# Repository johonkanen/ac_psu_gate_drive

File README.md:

# ac_psu_gate_drive

KiCad 10.0.7 conversion of the Proteus half-bridge gate-driver board
`gate_drive_power_asym_fb_v3_ee10` (2 × Si8271 isolated gate drivers, IXDD609 driving a hand-wound
toroid that supplies the two floating +/− gate rails; 22.4 × 34.9 mm, 2 layers). The board plugs face
to face into the ac_psu baseboard's J1–J4/J6/J8 (`~/dev/ac_psu_kicad`).

- `kicad/gate_drive.kicad_pro` – schematic (2 sheets, generated by `tools/sheets/sheetNN.py`) and PCB
  (`tools/make_pcb.sh`, rebuilt from the Proteus gerbers).
- `fab/` – JLCPCB BOM / CPL / gerbers and the hand-fit list (`fab/README.md`).
- `tools/check_all.sh` – every check (IPC netlist, ERC, footprints, board, DRC, IPC-356 diff,
  gerber round trip); must end with `ALL CHECKS PASSED`.
- `dcm/` – the DCM variant `gate_drive_power_dcm_fb_v3_ee10` (Q1 MMBT3904 primary switch instead of
  DRV3), converted the same way as a self-contained subproject; see `dcm/README.md`.
- `PLAN.md`, `STATUS.md`, `next_prompt.md` – plan, state and findings, next session prompt.

Tools: the proteus2kicad submodule `tools/p2k` (`git submodule update --init`); KiCad AppImage
`~/kicad/kicad-10.0.7-x86_64.AppImage` (never run it with `--version`).

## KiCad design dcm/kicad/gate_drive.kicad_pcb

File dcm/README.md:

# dcm – DCM variant of the gate-driver board

KiCad 10.0.7 conversion of the Proteus board `gate_drive_power_dcm_fb_v3_ee10` (2021-03-22). It is
the asym board of the repository root with the toroid primary driver replaced: instead of the
IXDD609 (DRV3) driving the primary through C12, a single NPN Q1 (MMBT3904) switches the primary
from 15V (J1 = 15V, J2 = collector), with the leakage/flyback energy clamped by R7 – D9 into
C9 ‖ R14 back to 15V. Same outline (22.4 × 34.9 mm), same J9 pinout, same gate drivers and rectifiers.

Converted 2026-11-03 (user: "convert the dcm version too"), same method and tools as the root board
(proteus2kicad playbook phases 0–4, submodule `../tools/p2k` through the symlink `tools/p2k`).
This folder is self-contained: its own `p2k_config.py`, so every tool run inside `dcm/` works on
this board. `tools/check_all.sh` must end with `ALL CHECKS PASSED`.

## Sources (`source/`)

`/mnt/c/Users/jaarh/Sync/proteus_projektit/Projects/gate_drive_power_asym_fb/V3_ee10/dcm/`: the
`.pdsprj` (Proteus 8.12 SP0) and the CADCAM zip (unpacked to `source/cadcam/`; identical copies in
`Sync_backup` and `D:\Sync_vamuuskopio`). **No PDF print exists** for this project.

IPC-D-356A: 135 records, 26 nets, 43 parts, 16 vias 0.381/0.254, no N/C, no holes.
Against the asym board: removed DRV3, C7 (4.7u 1206), C12 (100n); added Q1 MMBT3904, R7 10k,
R13 2.2k, R14 10k, C9 100n, D9 ZLLS400TA (values from ROOT.DSN); R11 is now the base resistor
(was the PWM_TRANS pull-down; R13 is that now). C8, R9, R11 and D6 moved; the copper around the primary switch and 5 vias differ.

## How it differs from the root conversion

- **Pages without a PDF:** `tools/make_part_map.py` puts the parts of the asym PDF page 1 on sheet 1
  (identical parts and nets; `sheet01.py` is the root script) and all others on sheet 2. The Q1
  primary-switch block on sheet 2 is drawn from the IPC netlist, not from a Proteus drawing.
- Symbols: `Q_NPN` (KiCad Device:Q_NPN, pins 1=B 2=E 3=C) instead of IXDD609.
- Footprints: `gate_drive:SOT-23_Proteus` – KiCad SOT-23 with the pad centres on the Proteus land
  pattern (rows 2.3 mm apart; KiCad's own SOT-23 is off by 0.28 mm); no DFN-8.
- DRC: 14 accepted courtyard overlaps (root: 15) and one extra warning `track_dangling` – a 6.5 µm
  15V stub that is in the Proteus bottom-copper gerber itself (line 86), kept as drawn.

## Findings (reported, not changed)

1. **R7 = 10k in the clamp path.** Q1 collector → R7 10k → D9 → C9 ‖ R14 → 15V. With 10k in series
   the clamp takes only milliamps, so at turn-off the leakage-inductance energy is hardly clamped and
   the collector can ring well above the MMBT3904's 40 V V_CEO. A clamp resistor is usually a few
   ohms to tens of ohms; R14 10k across C9 is the usual bleed. Check the value fitted on the built
   boards (10R vs 10k?).
2. **Base drive / available power.** Base current from PWM_TRANS through R11 10k is about 0.26 mA at
   3.3 V (0.43 mA at 5 V); with h_FE ≈ 100 the collector current saturates at roughly 25–40 mA, far
   below the 200 mA rating. That caps the primary peak current and so the gate-supply power
   (two Si8271 outputs). R13 2.2k loads PWM_TRANS only (it is on the source side of R11).
3. **Toroid windings unknown for DCM.** Sheet 2's note gives the asym drawing's windings; the
   DCM project has no drawing/PDF, and a DCM flyback normally uses a different turns ratio and
   winding polarity. Note what is actually wound.
4. Root findings 3 (baseboard pins 25/39), 4 (J9 drill) and 5 (0603 4.7 µF DC bias) apply as well.

## JLC (`fab/`)

As the root board (`fab/README.md`). The root's user BOM decisions are applied: SI8271DB-ISR,
D6/D7 MMSZ5246BS-7-F 16 V (rails +14.5…16 / −3…−4.5 V). New: Q1 C20526, R13 C4190 (both basic).
**ZLLS400TA (C460267) has 2 in stock (2026-11-03 afternoon; 2012 in the morning)** – short for both
boards (DCM needs 5 per board, asym 4). Not changed (open question).

## Last verification (`tools/check_all.sh`, 2026-11-03)

```
erc: 0 errors, 2 warnings (reports/erc.rpt)
compare: parts 43/43 present, 0 missing, 0 extra; pins compared 119, wrong-net pins 0; IPC nets touched 26, complete 26
check_footprints: 43/43 parts fitted, 119 pads, 10 footprints, worst residual 0.039 mm (limit 0.05)
make_pcb: board rebuilt from scratch, byte-identical
check_board: 455 tracks, 16 vias, 8 zones
assign_nets: after zone fill: 26 groups, 0 shorts, 0 orphans, 0 opens, 0 items with a foreign net
drc: 22 violations, 0 shorts, 0 unconnected, 0 parity issues (14 courtyards_overlap accepted, 7 silk, 1 track_dangling)
ipc356_diff: matched 135 (119 pads incl. 0 N/C, 16 vias, 0 holes), 26 Proteus nets mapped 1:1, 0 mismatches
roundtrip: F.Cu only pad-shape clusters (69), B.Cu XOR 0.00 mm^2, drills 0 mismatches
ALL CHECKS PASSED
```

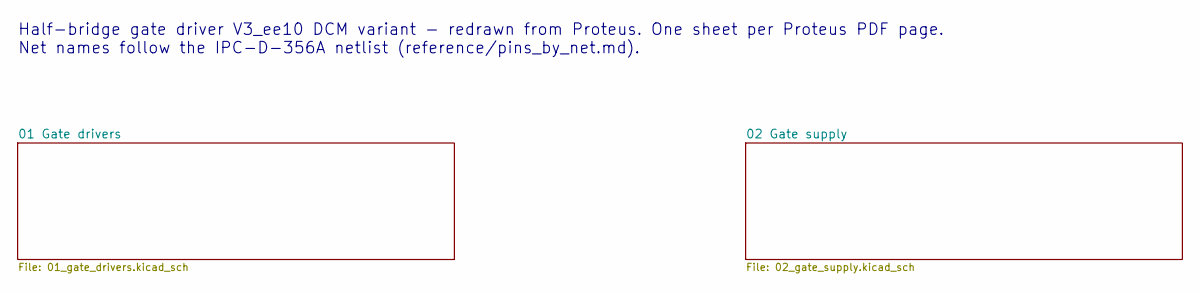
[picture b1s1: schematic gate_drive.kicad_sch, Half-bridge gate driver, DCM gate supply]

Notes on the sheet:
Half-bridge gate driver V3_ee10 DCM variant - redrawn from Proteus. One sheet per Proteus PDF page. Net names follow the IPC-D-356A netlist (reference/pins_by_net.md).

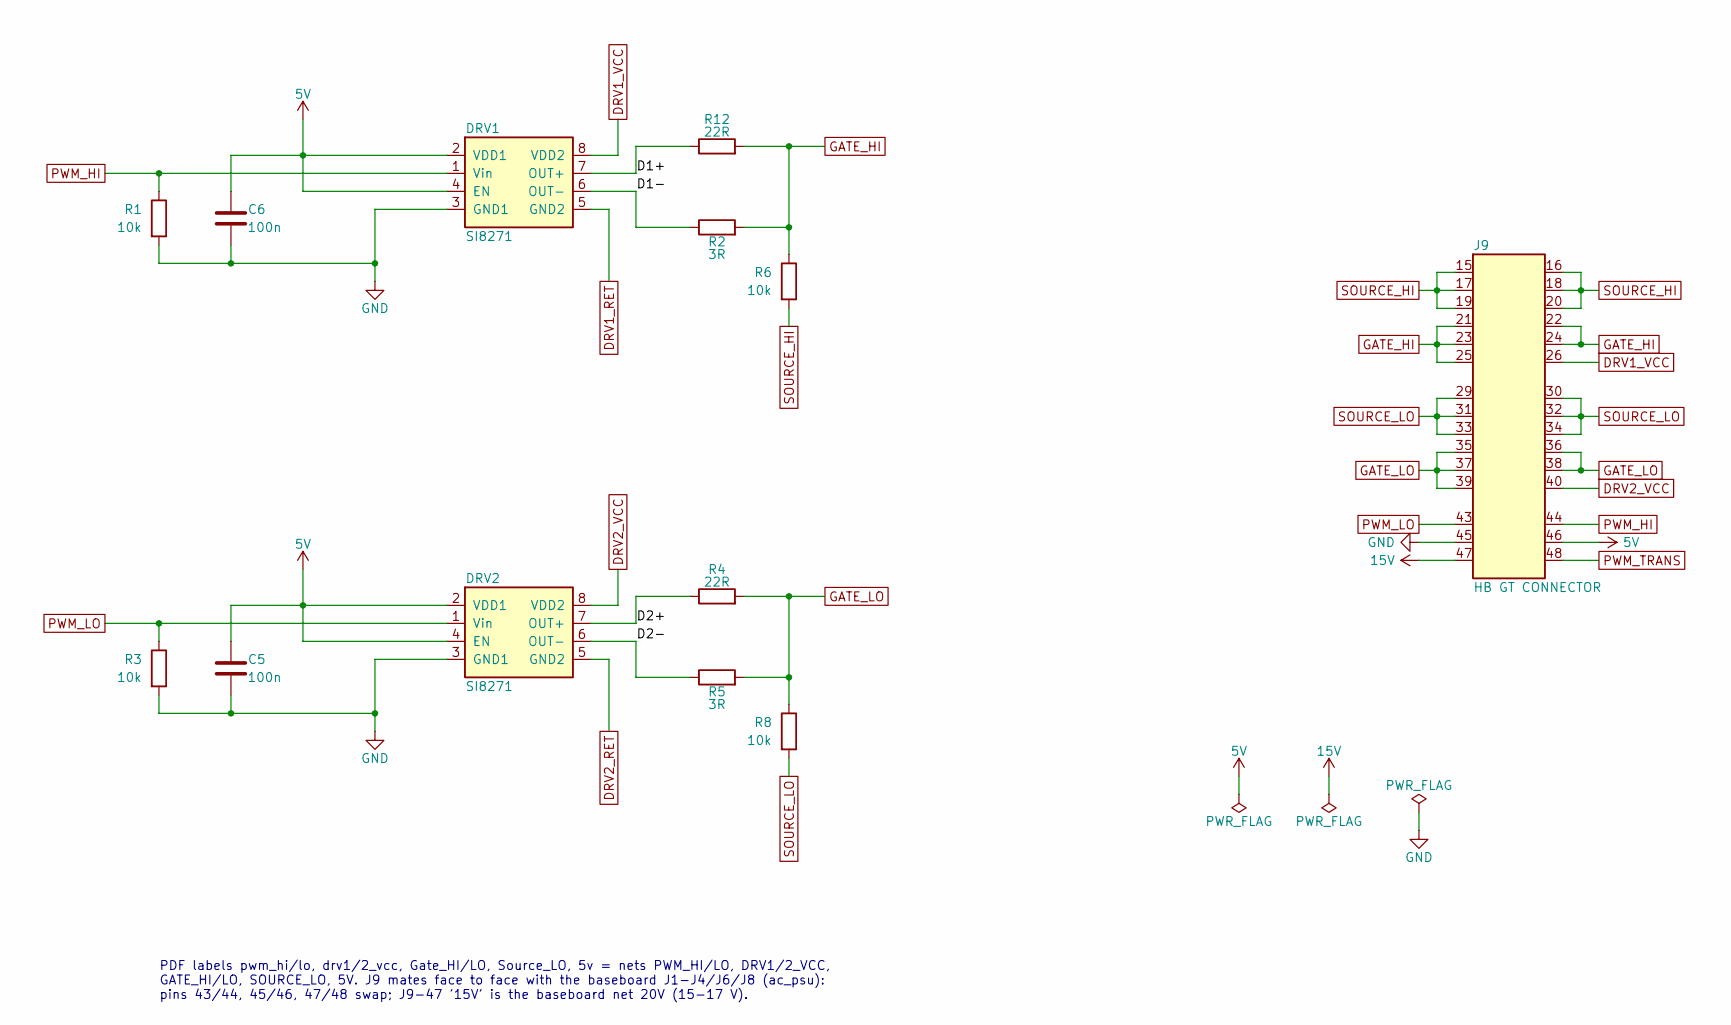
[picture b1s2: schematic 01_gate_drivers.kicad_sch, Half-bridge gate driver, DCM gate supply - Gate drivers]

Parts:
C5, C6: 100n; C_0603_1608Metric
DRV1, DRV2: SI8271; SOIC-8_3.9x4.9mm_P1.27mm_Proteus
J9: HB GT CONNECTOR; PinHeader_2x24_P1.27mm_Vertical_Pins15-48
R1, R3, R6, R8: 10k; R_0603_1608Metric
R2, R5: 3R; R_1206_3216Metric
R4, R12: 22R; R_1206_3216Metric

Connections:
5V: C5.2, C6.2, DRV1.2 (VDD1), DRV1.4 (EN), DRV2.2 (VDD1), DRV2.4 (EN), J9.46
15V: J9.47; also elsewhere on the board
/01 Gate drivers/D1+: DRV1.7 (OUT+), R12.1
/01 Gate drivers/D1-: DRV1.6 (OUT-), R2.1
/01 Gate drivers/D2+: DRV2.7 (OUT+), R4.1
/01 Gate drivers/D2-: DRV2.6 (OUT-), R5.1
DRV1_RET: DRV1.5 (GND2); also elsewhere on the board
DRV1_VCC: DRV1.8 (VDD2), J9.26; also elsewhere on the board
DRV2_RET: DRV2.5 (GND2); also elsewhere on the board
DRV2_VCC: DRV2.8 (VDD2), J9.40; also elsewhere on the board
GATE_HI: J9.21, J9.22, J9.23, J9.24, J9.25, R2.2, R6.1, R12.2
GATE_LO: J9.35, J9.36, J9.37, J9.38, J9.39, R4.2, R5.2, R8.1
GND: C5.1, C6.1, DRV1.3 (GND1), DRV2.3 (GND1), J9.45, R1.2, R3.2; also elsewhere on the board
PWM_HI: DRV1.1 (Vin), J9.44, R1.1
PWM_LO: DRV2.1 (Vin), J9.43, R3.1
PWM_TRANS: J9.48; also elsewhere on the board
SOURCE_HI: J9.15, J9.16, J9.17, J9.18, J9.19, J9.20, R6.2; also elsewhere on the board
SOURCE_LO: J9.29, J9.30, J9.31, J9.32, J9.33, J9.34, R8.2; also elsewhere on the board

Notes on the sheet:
PDF labels pwm_hi/lo, drv1/2_vcc, Gate_HI/LO, Source_LO, 5v = nets PWM_HI/LO, DRV1/2_VCC, GATE_HI/LO, SOURCE_LO, 5V. J9 mates face to face with the baseboard J1-J4/J6/J8 (ac_psu): pins 43/44, 45/46, 47/48 swap; J9-47 '15V' is the baseboard net 20V (15-17 V).

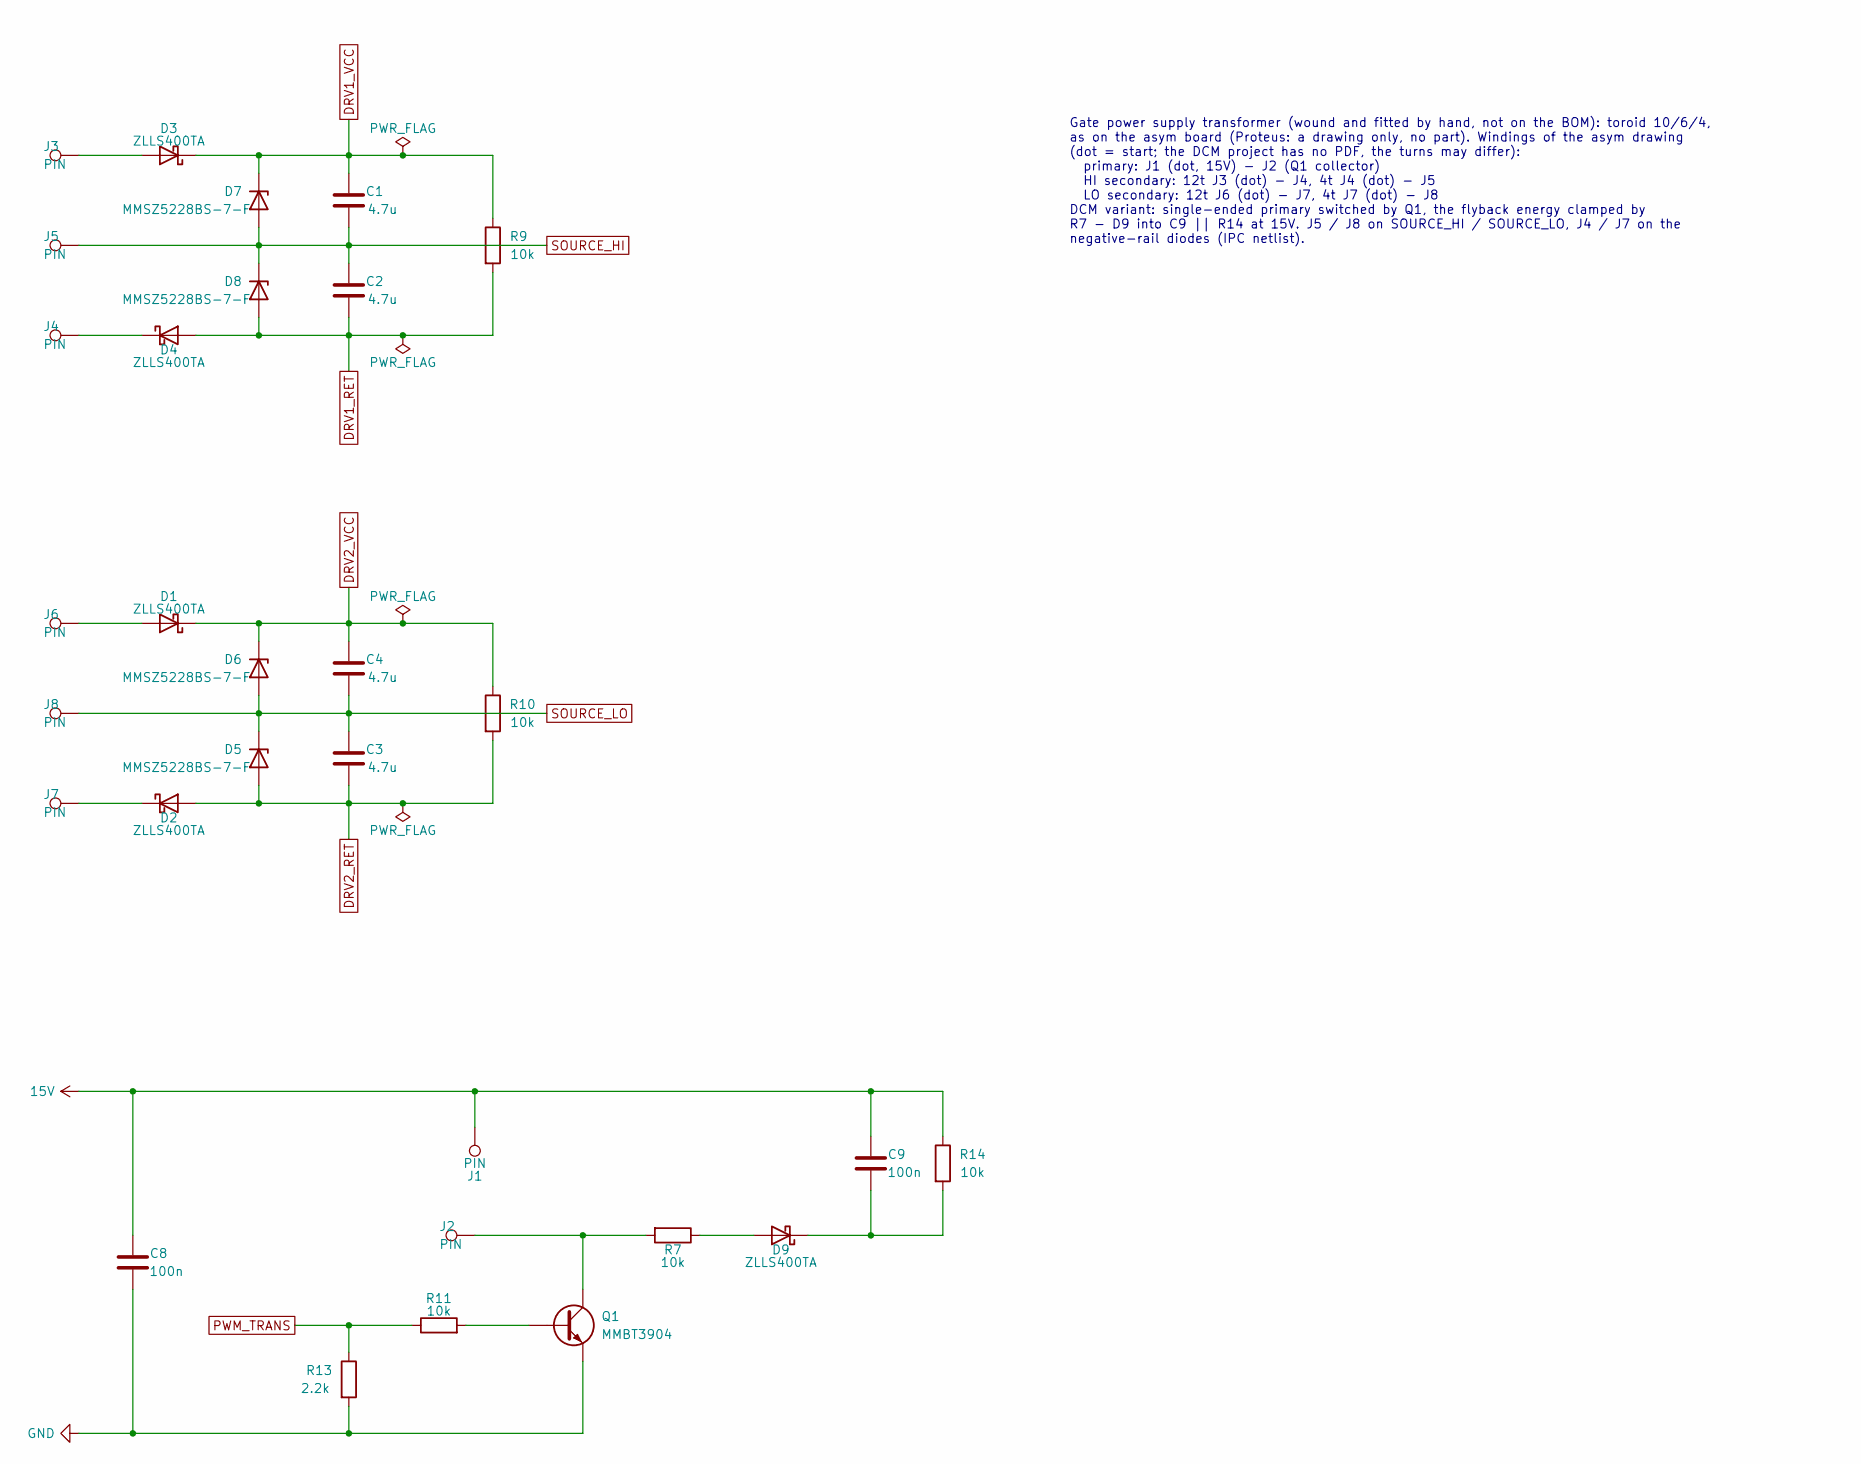
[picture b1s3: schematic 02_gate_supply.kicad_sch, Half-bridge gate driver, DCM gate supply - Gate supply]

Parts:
C1, C2, C3, C4: 4.7u; C_0603_1608Metric
C8: 100n; C_1206_3216Metric_Pad1.33x1.80mm_HandSolder
C9: 100n; C_0603_1608Metric
D1, D3, D4, D9: ZLLS400TA; D_SOD-323_AC
D2: ZLLS400TA; D_SOD-323_AC_Proteus
D5, D6, D7, D8: MMSZ5228BS-7-F; D_SOD-323_AC
J1, J2, J3, J4, J5, J6, J7, J8: PIN; WirePad_D1.27mm_Drill0.762mm
Q1: MMBT3904; SOT-23_Proteus
R7, R9, R10, R11, R14: 10k; R_0603_1608Metric
R13: 2.2k; R_0603_1608Metric

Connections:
15V: C8.2, C9.1, J1.1, R14.1; also elsewhere on the board
DRV1_RET: C2.2, D4.A, D8.A, R9.2; also elsewhere on the board
DRV1_VCC: C1.1, D3.C (K), D7.C (K), R9.1; also elsewhere on the board
DRV2_RET: C3.2, D2.A, D5.A, R10.2; also elsewhere on the board
DRV2_VCC: C4.1, D1.C (K), D6.C (K), R10.1; also elsewhere on the board
GND: C8.1, Q1.2 (E), R13.2; also elsewhere on the board
unnamed: D1.A, J6.1
unnamed: D2.C (K), J7.1
unnamed: D3.A, J3.1
unnamed: D4.C (K), J4.1
unnamed: C9.2, D9.C (K), R14.2
unnamed: D9.A, R7.1
unnamed: Q1.1 (B), R11.2
unnamed: J2.1, Q1.3 (C), R7.2
PWM_TRANS: R11.1, R13.1; also elsewhere on the board
SOURCE_HI: C1.2, C2.1, D7.A, D8.C (K), J5.1; also elsewhere on the board
SOURCE_LO: C3.1, C4.2, D5.C (K), D6.A, J8.1; also elsewhere on the board

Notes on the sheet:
Gate power supply transformer (wound and fitted by hand, not on the BOM): toroid 10/6/4, as on the asym board (Proteus: a drawing only, no part). Windings of the asym drawing (dot = start; the DCM project has no PDF, the turns may differ): primary: J1 (dot, 15V) - J2 (Q1 collector) HI secondary: 12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

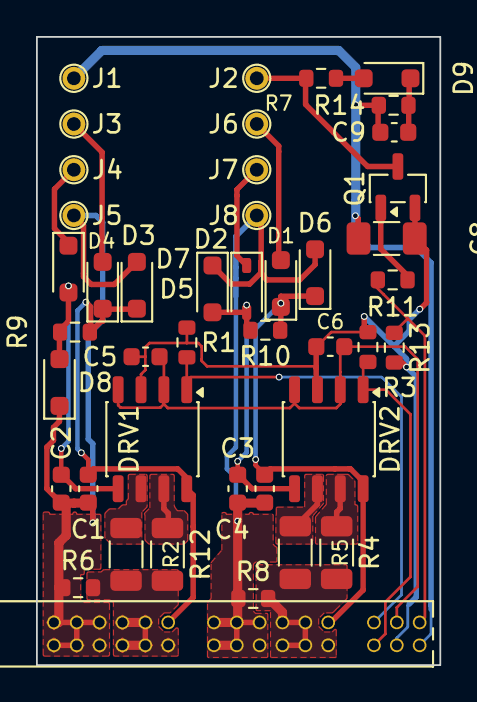
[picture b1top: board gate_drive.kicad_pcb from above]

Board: 2 copper layers, 22.4 x 34.9 mm, 43 parts (0 on the bottom side), 26 nets.

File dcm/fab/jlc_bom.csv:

Comment,Designator,Footprint,JLCPCB Part #
10k,"R1,R3,R6,R7,R8,R9,R10,R11,R14",0603,C25804
2.2k,R13,0603,C4190
22R,"R4,R12",1206,C17958
3R,"R2,R5",1206,C17939
100nF 50V X7R,"C5,C6,C9",0603,C14663
4.7uF 25V X5R,"C1,C2,C3,C4",0603,C5360844
100nF 50V X7R,C8,1206,C24497
ZLLS400TA,"D1,D2,D3,D4,D9",SOD-323,C460267
MMSZ5228BS-7-F,"D5,D8",SOD-323,C2895358
MMSZ5246BS-7-F,"D6,D7",SOD-323,C151819
MMBT3904,Q1,SOT-23,C20526
SI8271DB-ISR,"DRV1,DRV2",SOIC-8,C461855

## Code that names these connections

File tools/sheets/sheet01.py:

#!/usr/bin/env python3
"""Sheet 1 - gate drivers (PDF page 1): the isolated gate drivers DRV1 (high side, PWM_HI ->
GATE_HI) and DRV2 (low side, PWM_LO -> GATE_LO), Si8271, and the HB GT connector J9."""
from _common import *  # noqa: F401,F403

sh = sheet("01_gate_drivers.kicad_sch")


def si8271_cell(ref, UX, UY, pwm, r_pd, c_dec, vcc, ret, dp, dm, r_on, r_off, gate, r_gs, src):
    """Si8271 cell as drawn in the PDF. Input: pwm label with pull-down r_pd (pin 1 = pwm),
    VDD1 + EN on 5V with c_dec (pin 2 = 5V), GND1 on GND. Output: VDD2 = vcc, GND2 = ret
    (global labels, the supply comes from sheet 2), OUT+ -> local label dp -> r_on (pin 1),
    OUT- -> dm -> r_off (pin 1), both pin 2 on the gate label, r_gs (pin 1 gate, pin 2 src)."""
    u = sh.place("SI8271", ref, UX, UY, value="SI8271")
    VIN, VDD1, GND1, EN = (u.pin(n) for n in (1, 2, 3, 4))
    VDD2, OUTP, OUTM, GND2 = (u.pin(n) for n in (8, 7, 6, 5))
    # --- input side
    xl = UX - g(46)
    sh.wire(VIN, (xl, VIN[1]))
    sh.glabel(pwm, xl, VIN[1], 180)
    _, rt, rb = vert2(sh, "R", r_pd[0], UX - g(40), VIN[1] + g(5), r_pd[1], top=1, text="left")
    sh.wire((UX - g(40), VIN[1]), rt)
    sh.junction(UX - g(40), VIN[1])
    gnd_row = rb[1] + g(2)
    xv = UX - g(24)                     # 5V column: VDD1 and EN, C_dec beside it
    sh.wire(VDD1, (xv, VDD1[1]))
    sh.wire(EN, (xv, EN[1]))
    sh.wire((xv, VDD1[1] - g(4)), (xv, EN[1]))
    sh.junction(xv, VDD1[1])
    power_at(sh, "5V", (xv, VDD1[1] - g(4)), "up")
    _, ct, cb = vert2(sh, "C", c_dec[0], UX - g(32), gnd_row - g(5), c_dec[1], top=2)
    sh.wire(ct, (UX - g(32), VDD1[1]), (xv, VDD1[1]))
    xg = UX - g(16)
    sh.wire(GND1, (xg, GND1[1]), (xg, gnd_row))
    sh.wire(rb, (rb[0], gnd_row), (xg, gnd_row))
    sh.wire(cb, (cb[0], gnd_row))
    sh.junction(cb[0], gnd_row)
    sh.junction(xg, gnd_row)
    sh.wire((xg, gnd_row), (xg, gnd_row + g(2)))
    power_at(sh, "GND", (xg, gnd_row + g(2)), "down")
    # --- output side
    q = (VDD2[0] + g(3), VDD2[1] - g(4))
    sh.wire(VDD2, (q[0], VDD2[1]), q)
    sh.glabel(vcc, q[0], q[1], 90)
    q = (GND2[0] + g(2), GND2[1] + g(8))
    sh.wire(GND2, (q[0], GND2[1]), q)
    sh.glabel(ret, q[0], q[1], 270)
    label_right(sh, dp, OUTP, 5)
    label_right(sh, dm, OUTM, 5)
    ya, yb = OUTP[1] - g(3), OUTM[1] + g(4)
    _, a1, a2 = horiz2(sh, "R", r_on[0], UX + g(22), ya, r_on[1], left=1, text="above")
    _, b1, b2 = horiz2(sh, "R", r_off[0], UX + g(22), yb, r_off[1], left=1, text="below")
    sh.wire(right(OUTP, 5), (right(OUTP, 5)[0], ya), a1)
    sh.wire(right(OUTM, 5), (right(OUTM, 5)[0], yb), b1)
    xj = UX + g(30)
    sh.wire(a2, (xj, a2[1]), (xj, b2[1]))
    sh.wire(b2, (xj, b2[1]))
    sh.junction(xj, b2[1])
    glabel_right(sh, gate, (xj, a2[1]), 4)
    sh.junction(xj, a2[1])
    _, rt, rb = vert2(sh, "R", r_gs[0], xj, b2[1] + g(6), r_gs[1], top=1, text="left")
    sh.wire((xj, b2[1]), rt)
    q = down(rb, 2)
    sh.wire(rb, q)
    sh.glabel(src, q[0], q[1], 270)
    return u


# PDF labels pwm_hi / drv1_vcc / Gate_HI / ... = IPC nets PWM_HI / DRV1_VCC / GATE_HI / ...
si8271_cell("DRV1", g(60), g(40), "PWM_HI", ("R1", "10k"), ("C6", "100n"), "DRV1_VCC", "DRV1_RET",
            "D1+", "D1-", ("R12", "22R"), ("R2", "3R"), "GATE_HI", ("R6", "10k"), "SOURCE_HI")
si8271_cell("DRV2", g(60), g(90), "PWM_LO", ("R3", "10k"), ("C5", "100n"), "DRV2_VCC", "DRV2_RET",
            "D2+", "D2-", ("R4", "22R"), ("R5", "3R"), "GATE_LO", ("R8", "10k"), "SOURCE_LO")

# --- J9 HB GT connector -------------------------------------------------------------------
JX, JY = g(170), g(65)
j9 = sh.place("HB_GT_CONNECTOR", "J9", JX, JY, value="HB GT CONNECTOR")
P = j9.pin
bus_group(sh, [P(15), P(17), P(19)], P(17), "left", label="SOURCE_HI")
bus_group(sh, [P(16), P(18), P(20)], P(18), "right", label="SOURCE_HI")
bus_group(sh, [P(21), P(23), P(25)], P(23), "left", label="GATE_HI")
bus_group(sh, [P(22), P(24)], P(24), "right", label="GATE_HI")
glabel_right(sh, "DRV1_VCC", P(26), 4)
bus_group(sh, [P(29), P(31), P(33)], P(31), "left", label="SOURCE_LO")
bus_group(sh, [P(30), P(32), P(34)], P(32), "right", label="SOURCE_LO")
bus_group(sh, [P(35), P(37), P(39)], P(37), "left", label="GATE_LO")
bus_group(sh, [P(36), P(38)], P(38), "right", label="GATE_LO")
glabel_right(sh, "DRV2_VCC", P(40), 4)
glabel_left(sh, "PWM_LO", P(43), 4)
glabel_right(sh, "PWM_HI", P(44), 4)
q = left(P(45), 4)
sh.wire(P(45), q)
power_at(sh, "GND", q, "left")
q = right(P(46), 4)
sh.wire(P(46), q)
power_at(sh, "5V", q, "right")
q = left(P(47), 4)
sh.wire(P(47), q)
power_at(sh, "15V", q, "left")
glabel_right(sh, "PWM_TRANS", P(48), 4)
# the rails enter the board on J9 (passive pins): power flags
flagged_power(sh, "5V", JX - g(30), JY + g(40))
flagged_power(sh, "15V", JX - g(20), JY + g(40))
flagged_power(sh, "GND", JX - g(10), JY + g(46))

sh.text("PDF labels pwm_hi/lo, drv1/2_vcc, Gate_HI/LO, Source_LO, 5v = nets PWM_HI/LO, DRV1/2_VCC,\n"
        "GATE_HI/LO, SOURCE_LO, 5V. J9 mates face to face with the baseboard J1-J4/J6/J8 (ac_psu):\n"
        "pins 43/44, 45/46, 47/48 swap; J9-47 '15V' is the baseboard net 20V (15-17 V).", g(20), g(130))
sh.save()
print("sheet01: written")
